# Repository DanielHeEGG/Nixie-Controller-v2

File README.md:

# Nixie Clock Controller v2
The most overpowered 6-tube nixie clock controller ever created.

For more details on the project, see [Hackaday Page](https://hackaday.io/project/181819-nixie-clock-controller-v2).

Sockets designed to work with this controller are in the [NCv2-Sockets](https://github.com/DanielHeEGG/NCv2-Sockets) repo.

Firmware files are in the [NCv2-Firmware](https://github.com/DanielHeEGG/NCv2-Firmware) repo.

> **WARNING:**
> This project contains EXPOSED and UNMARKED HIGH VOLTAGE contacts, replicate at your own risk.
## License
This project is licensed under the [Creative Commons Attribution-ShareAlike 4.0 International License](http://creativecommons.org/licenses/by-sa/4.0/).

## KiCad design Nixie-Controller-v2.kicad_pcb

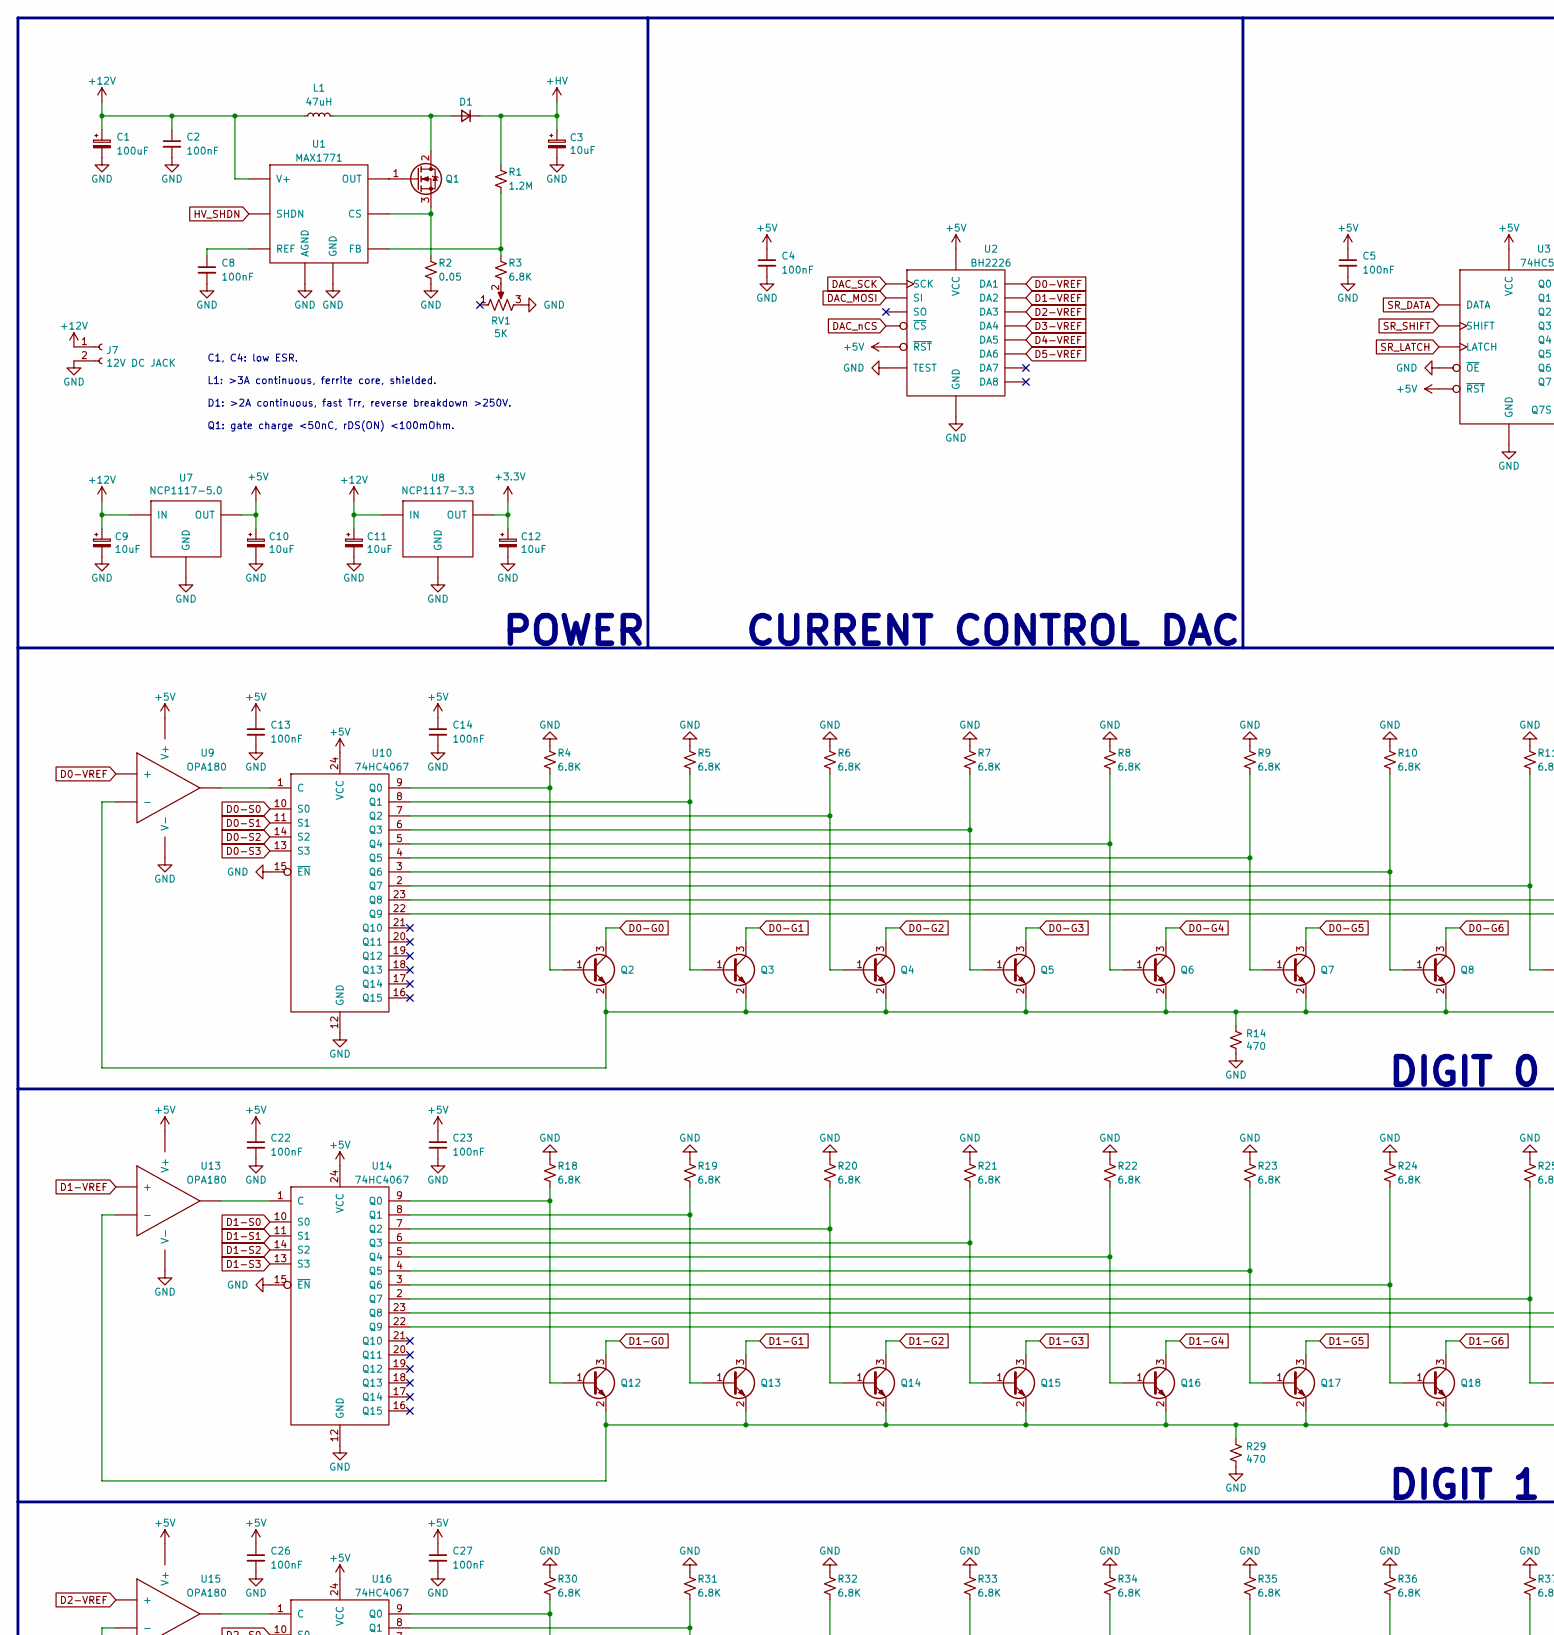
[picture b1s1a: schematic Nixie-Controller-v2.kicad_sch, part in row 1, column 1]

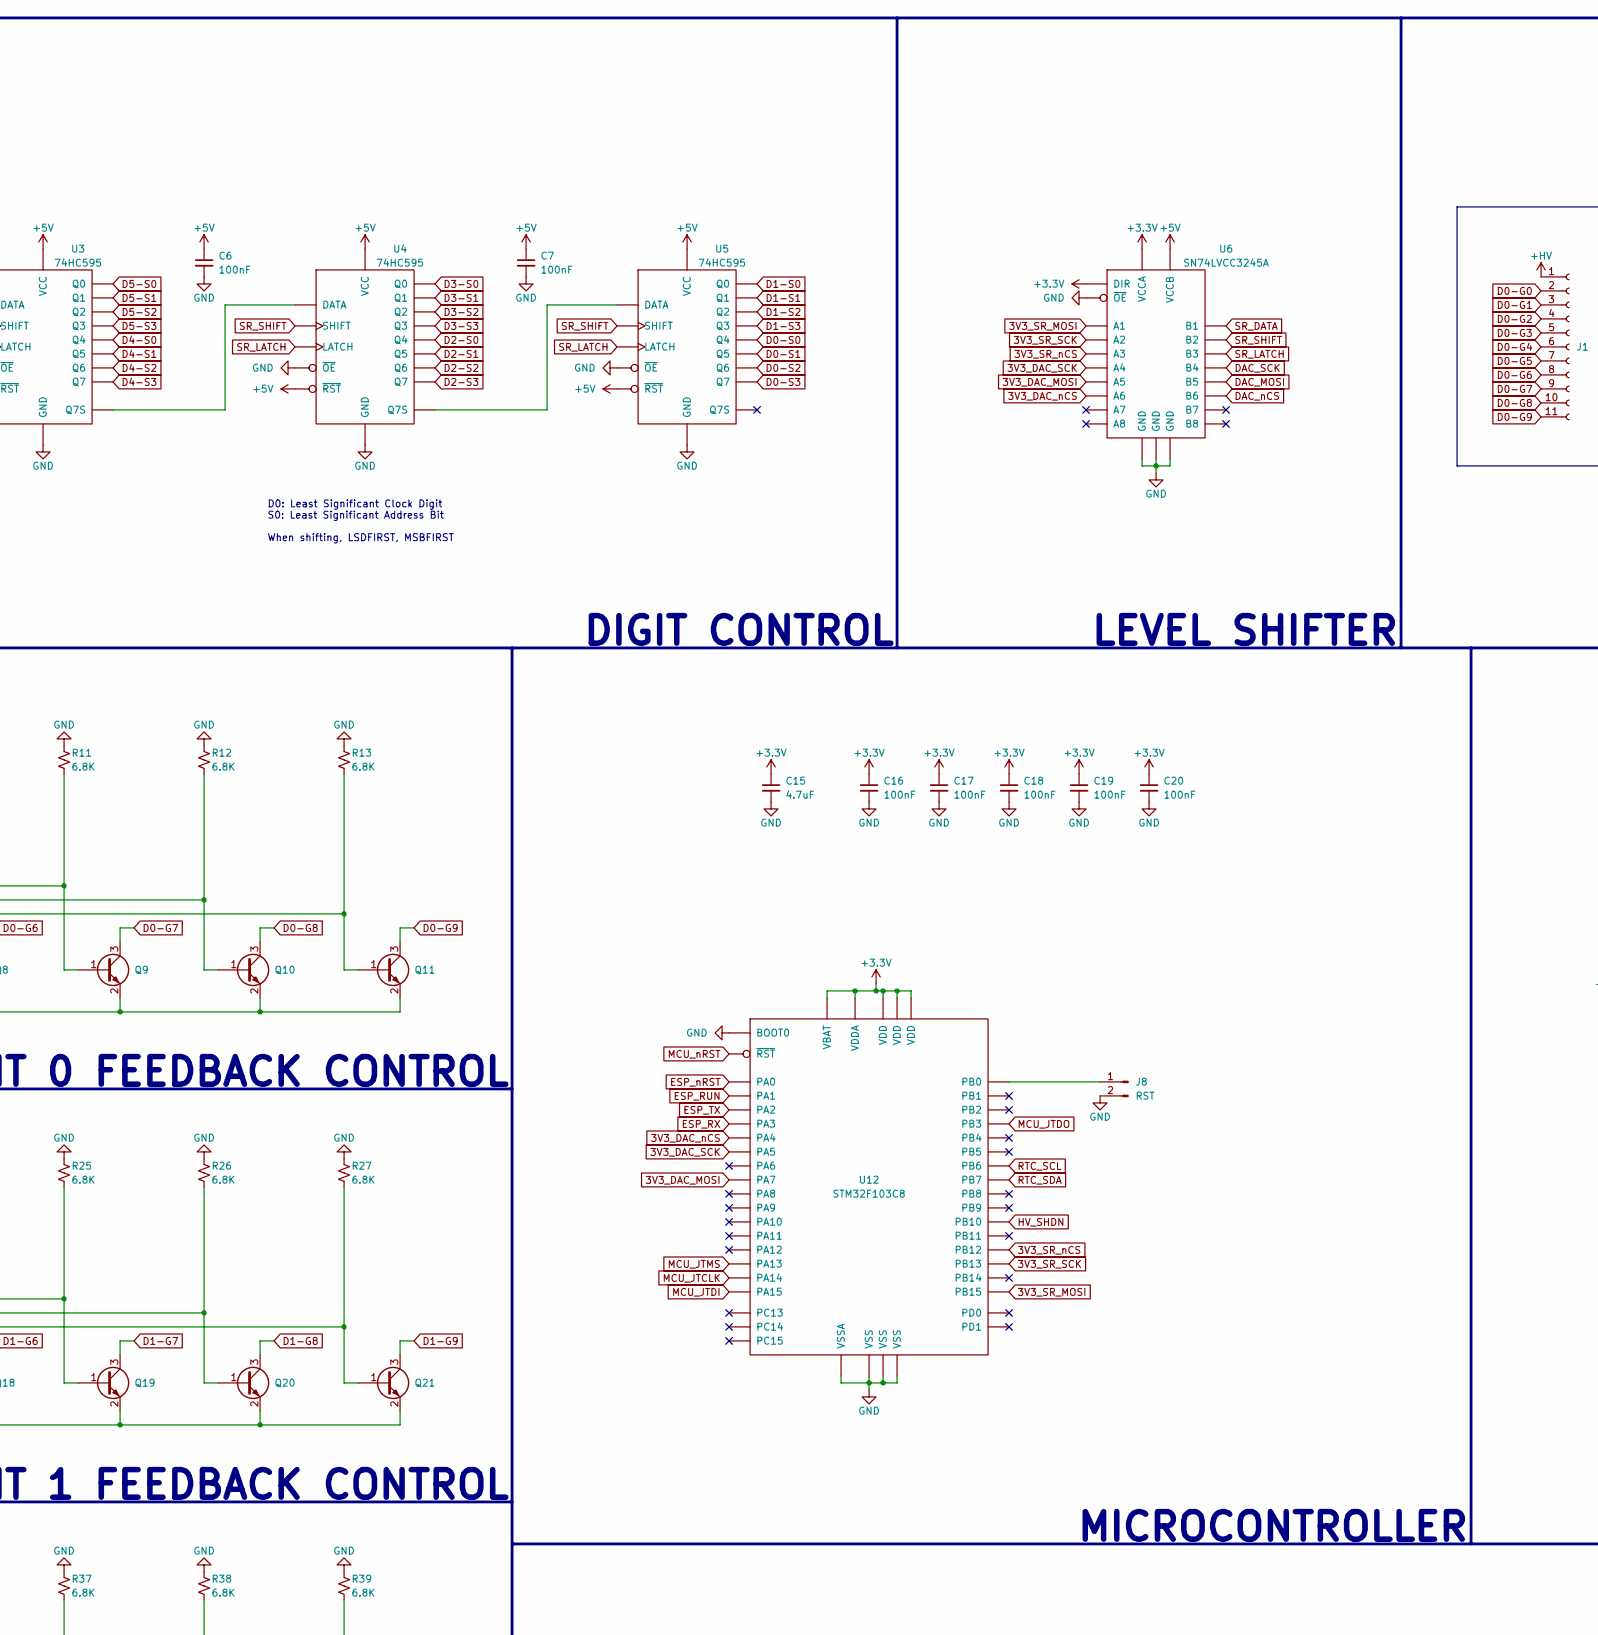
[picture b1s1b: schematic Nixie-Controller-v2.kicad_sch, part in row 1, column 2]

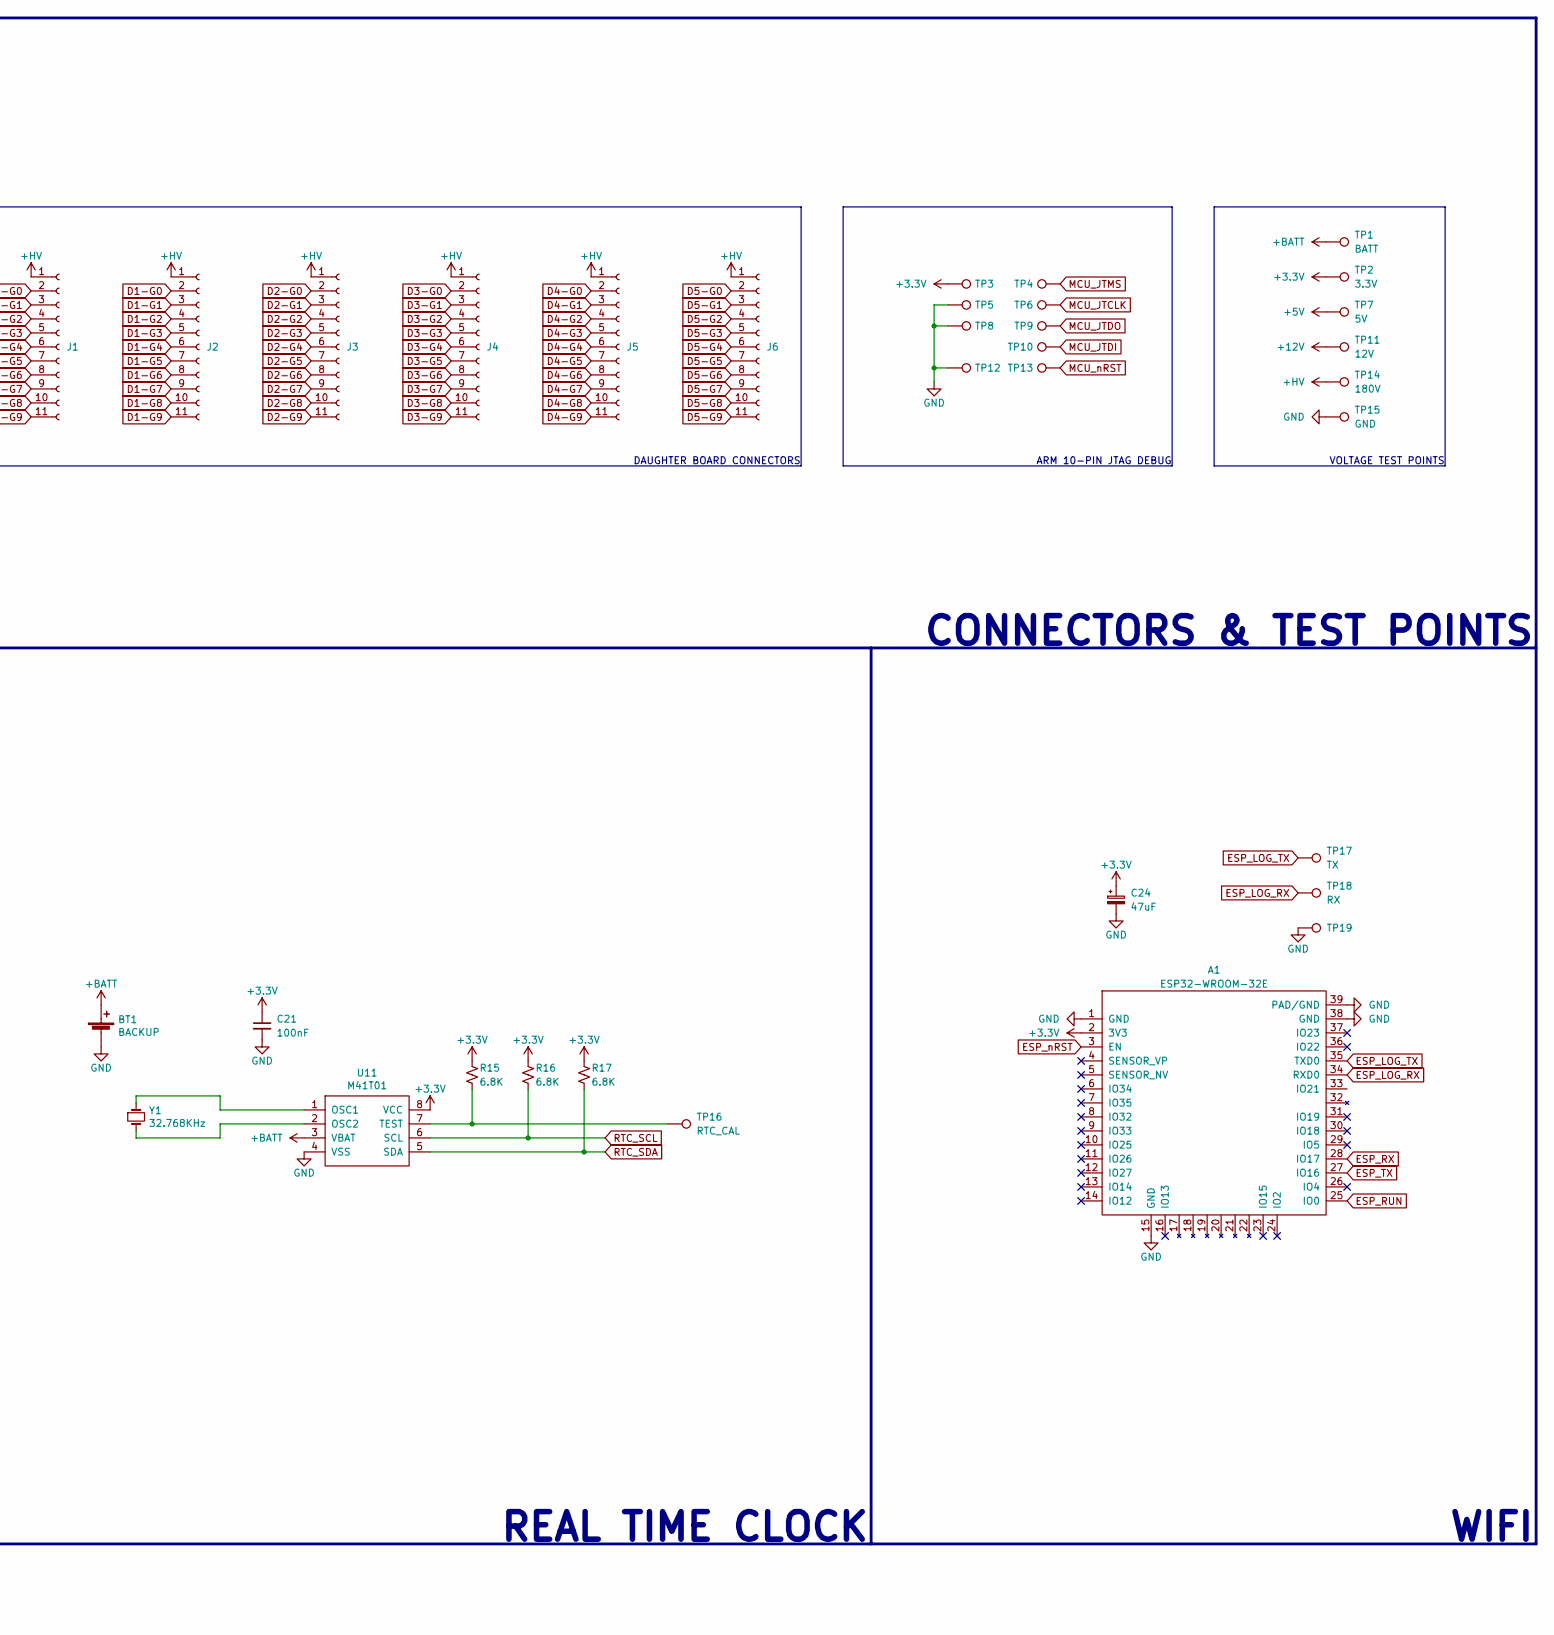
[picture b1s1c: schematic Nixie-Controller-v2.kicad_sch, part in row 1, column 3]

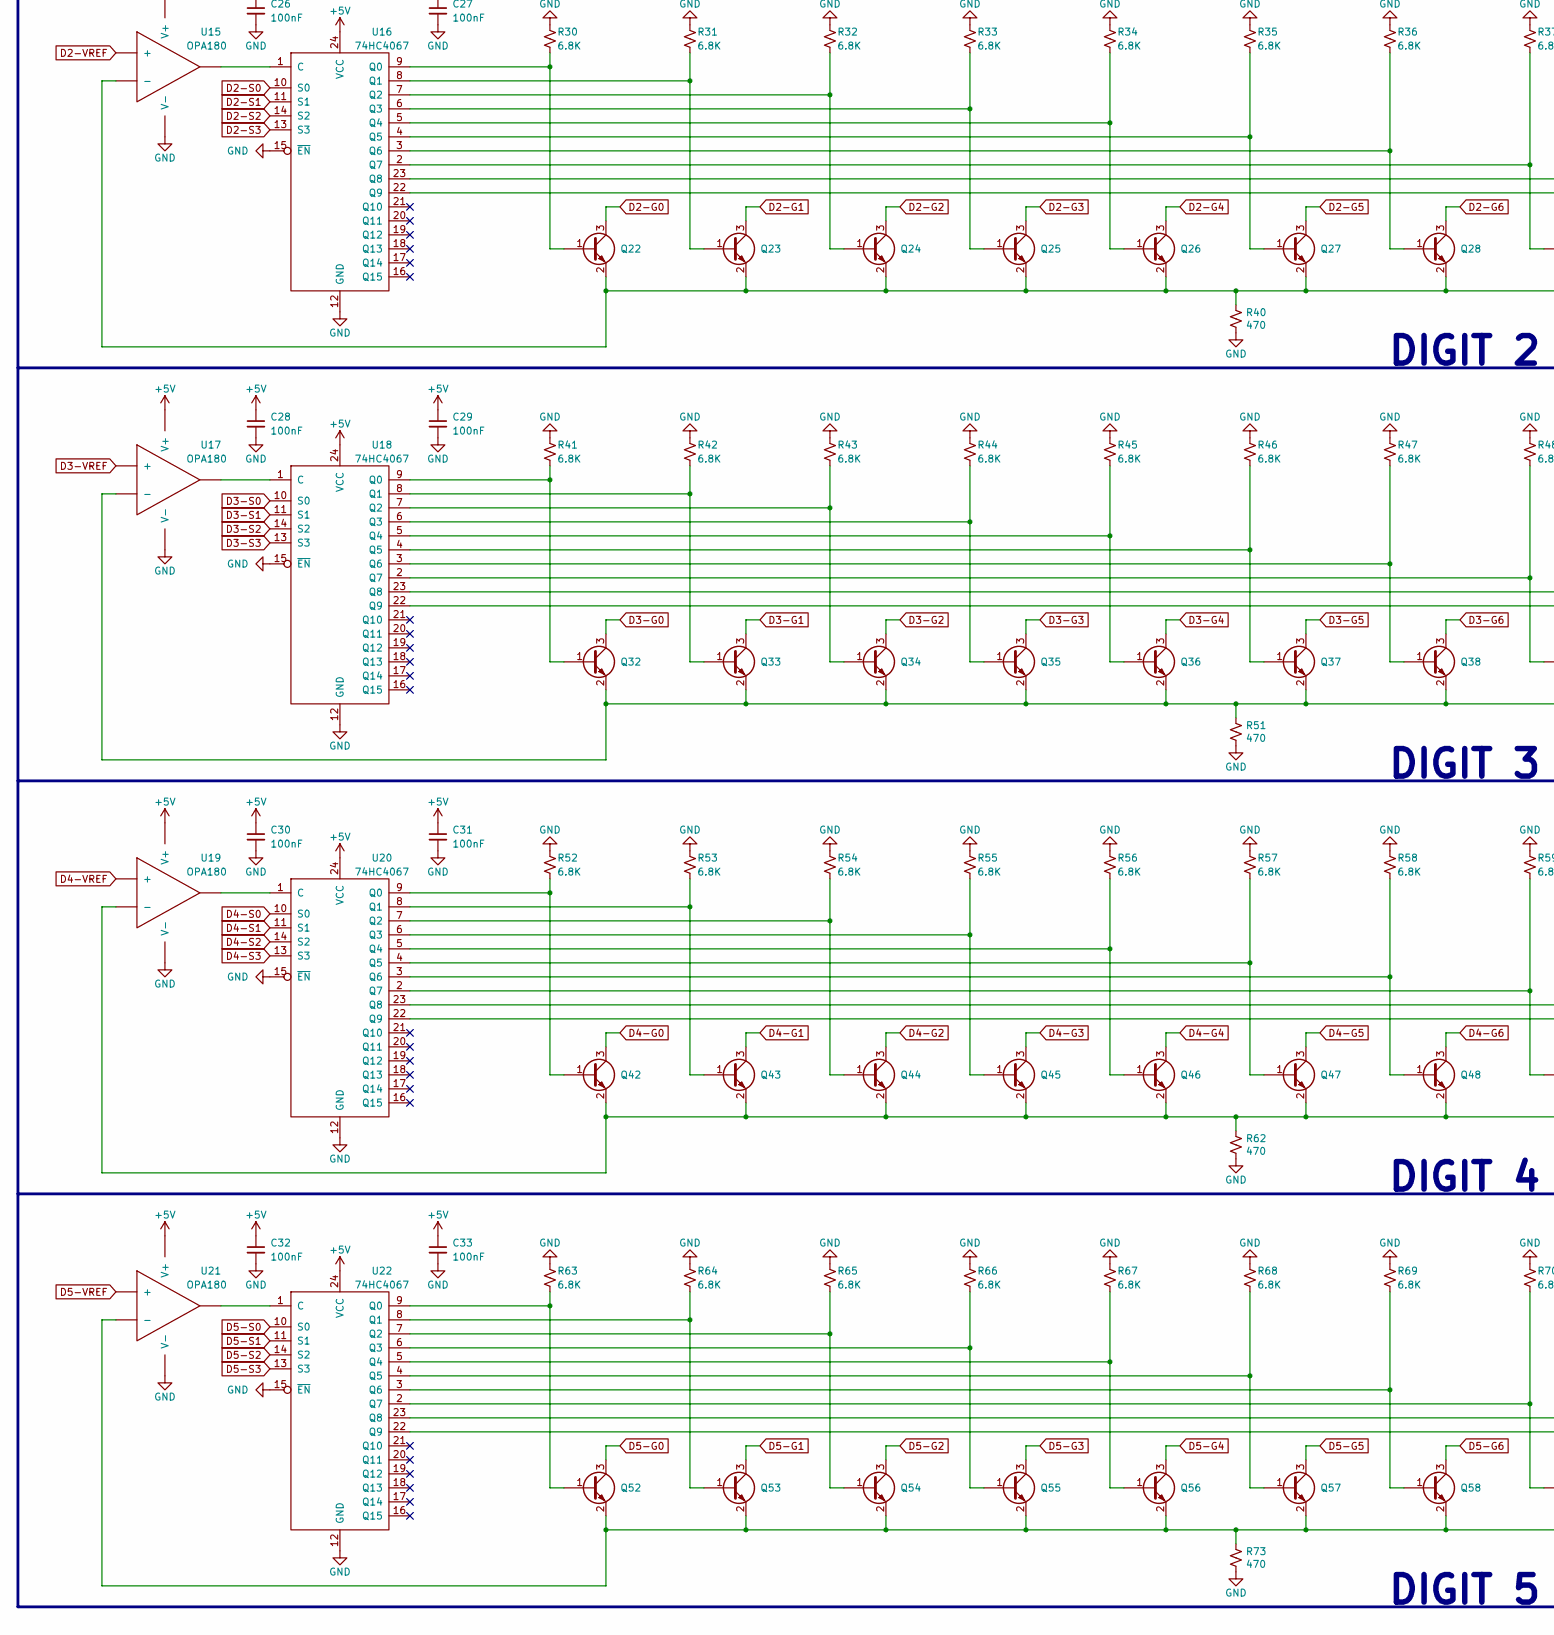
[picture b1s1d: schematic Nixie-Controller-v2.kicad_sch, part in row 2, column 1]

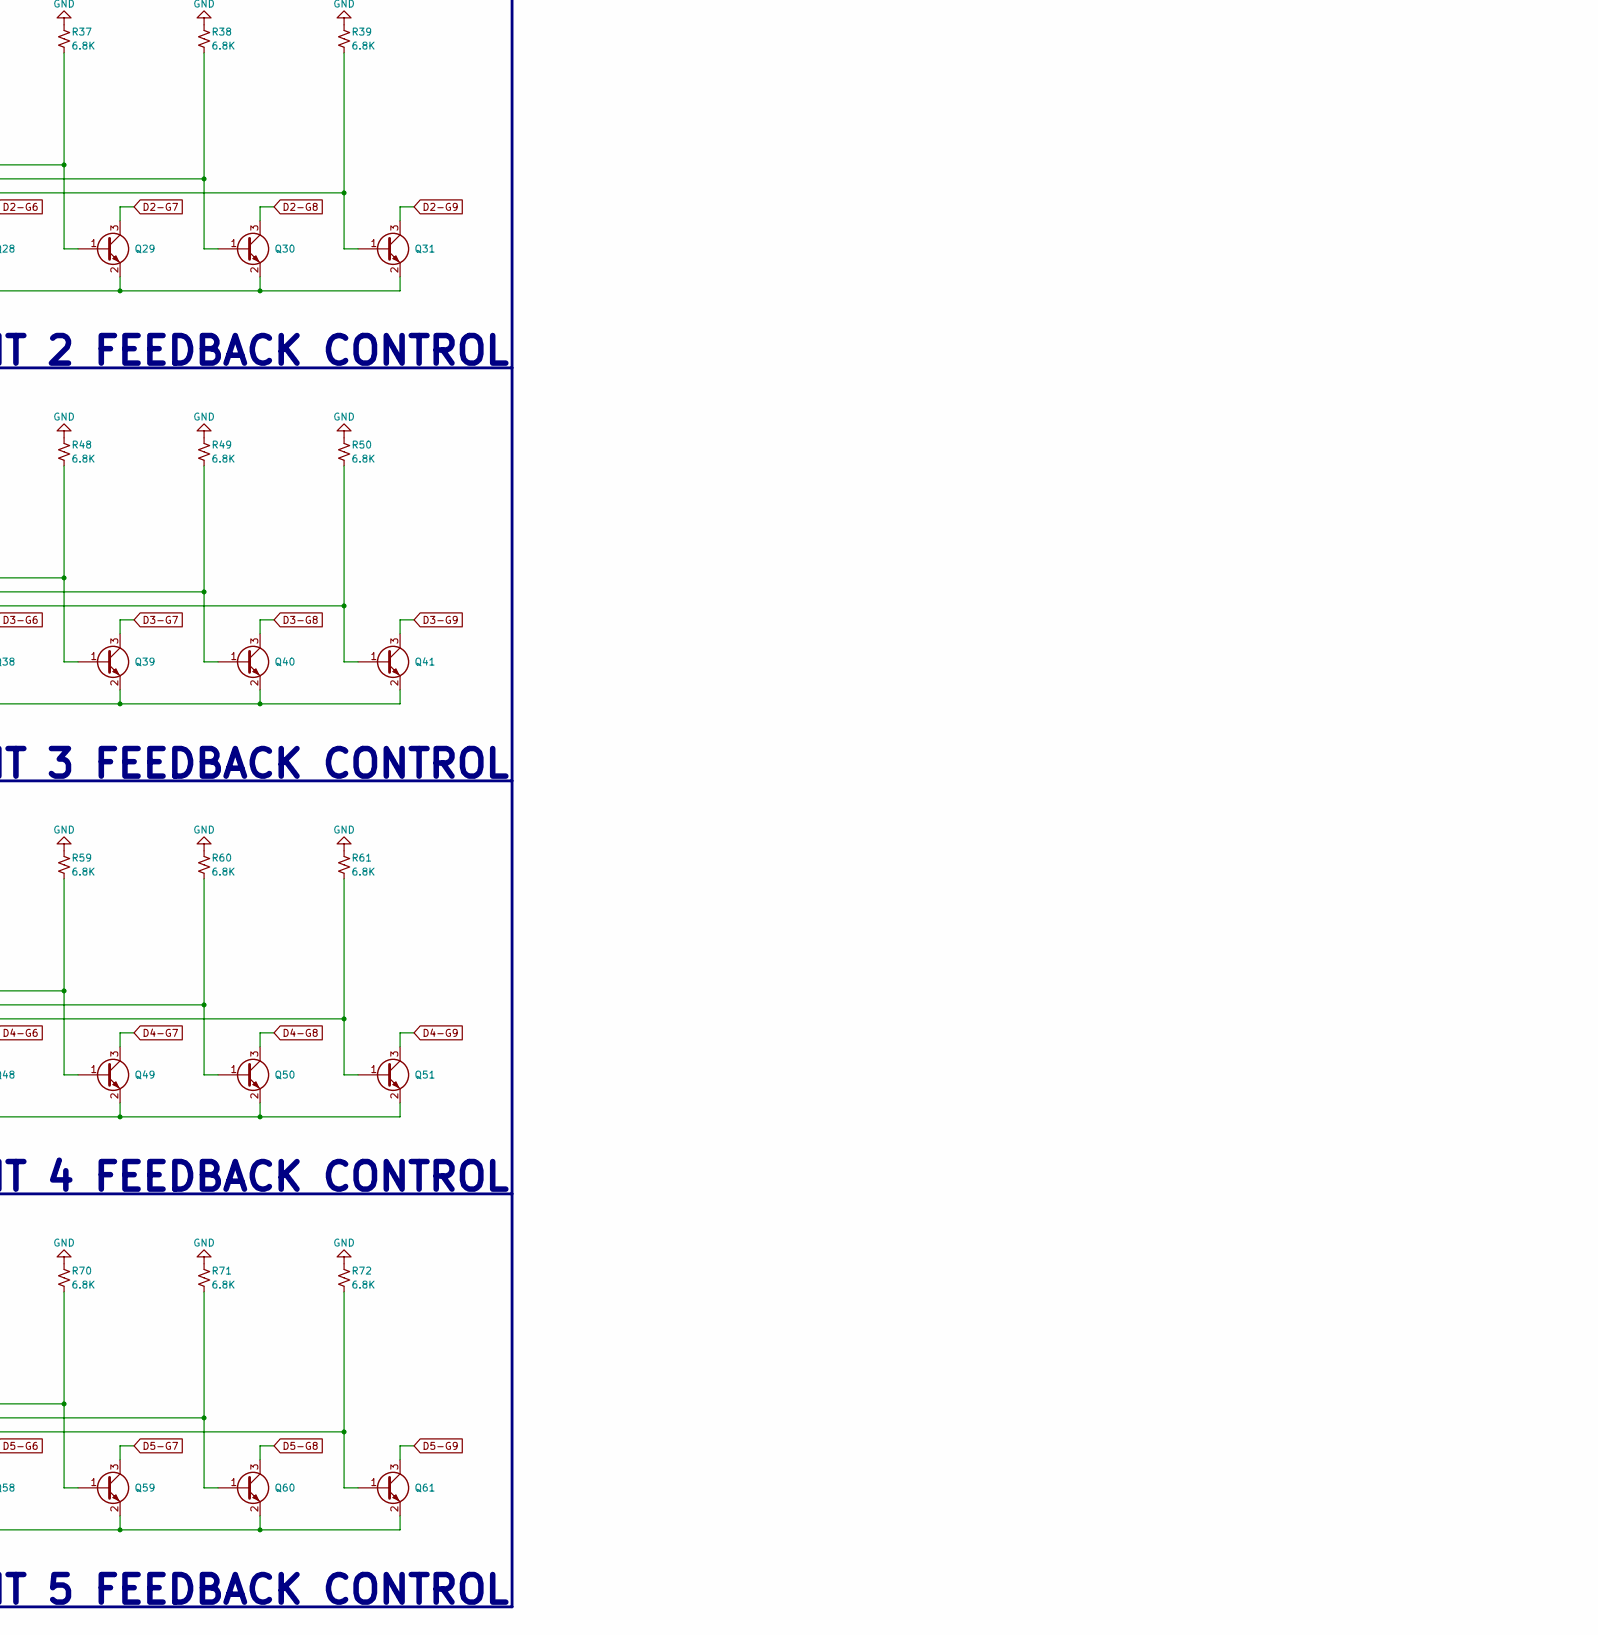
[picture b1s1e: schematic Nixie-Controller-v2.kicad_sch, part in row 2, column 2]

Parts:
A1: ESP32-WROOM-32E; ESP32-WROOM-32
BT1: BACKUP; BatteryHolder_Keystone_1058_1x2032; Part# 1058
C1: 100uF; CP_EIA-7343-43_Kemet-X; Part# T510X107M020ATE045
C2, C4, C5, C6, C7, C8, C13, C14, C16, C17, C18, C19, C20, C21, C22, C23, C26, C27, C28, C29, C30, C31, C32, C33: 100nF; C_0402_1005Metric; Part# CC0402KRX7R8BB104
C3: 10uF; CP_Elec_10x10; Part# UUX2E100MNL1GS
C9, C10, C11, C12: 10uF; CP_Elec_6.3x7.7; Part# UUL1H100MCL1GS
C15: 4.7uF; C_0603_1608Metric; Part# CC0603MRX5R5BB475
C24: 47uF; CP_Elec_5x5.3; Part# UWF0J470MCL1GB
D1: D_SMB; Part# ES2F
J1, J2, J3, J4, J5, J6: PinSocket_1x11_P2.54mm_Vertical
J7: 12V DC JACK; BarrelJack_Horizontal
J8: RST; PinHeader_1x02_P2.54mm_Vertical
L1: 47uH; L_Bourns_SRR1210A; Part# SRR1210A-470M
Q1: TO-252-2; Part# IXFY26N30X3
Q2, Q3, Q4, Q5, Q6, Q7, Q8, Q9, Q10, Q11, Q12, Q13, Q14, Q15, Q16, Q17, Q18, Q19, Q20, Q21, Q22, Q23, Q24, Q25, Q26, Q27, Q28, Q29, Q30, Q31, Q32, Q33, Q34, Q35, Q36, Q37, Q38, Q39, Q40, Q41, Q42, Q43, Q44, Q45, Q46, Q47, Q48, Q49, Q50, Q51, Q52, Q53, Q54, Q55, Q56, Q57, Q58, Q59, Q60, Q61: SOT-23; Part# MMBTA42
R1: 1.2M; R_0805_2012Metric; Part# RC0805FR-071M2L
R2: 0.05; R_2010_5025Metric; Part# PE2010FKE070R05L
R3, R4, R5, R6, R7, R8, R9, R10, R11, R12, R13, R15, R16, R17, R18, R19, R20, R21, R22, R23, R24, R25, R26, R27, R30, R31, R32, R33, R34, R35, R36, R37, R38, R39, R41, R42, R43, R44, R45, R46, R47, R48, R49, R50, R52, R53, R54, R55, R56, R57, R58, R59, R60, R61, R63, R64, R65, R66, R67, R68, R69, R70, R71, R72: 6.8K; R_0402_1005Metric; Part# RC0402FR-076K8L
R14, R29, R40, R51, R62, R73: 470; R_0402_1005Metric; Part# RC0402FR-07470RL
RV1: 5K; Potentiometer_Bourns_3214J_Horizontal; Part# 3214J-1-502E
TP1: BATT; TestPoint_Pad_D1.5mm
TP2: 3.3V; TestPoint_Pad_D1.5mm
TP3, TP4, TP5, TP6, TP8, TP9, TP10, TP12, TP13, TP19: TestPoint_Pad_D1.5mm
TP7: 5V; TestPoint_Pad_D1.5mm
TP11: 12V; TestPoint_Pad_D1.5mm
TP14: 180V; TestPoint_Pad_D1.5mm
TP15: GND; TestPoint_Pad_D1.5mm
TP16: RTC_CAL; TestPoint_Pad_D1.5mm
TP17: TX; TestPoint_Pad_D1.5mm
TP18: RX; TestPoint_Pad_D1.5mm
U1: MAX1771; SOIC-8_3.9x4.9mm_P1.27mm; Part# MAX1771CSA
U2: BH2226; SOIC-16_4.55x10.3mm_P1.27mm; Part# BH2226F-E2
U3, U4, U5: 74HC595; SOIC-16_3.9x9.9mm_P1.27mm; Part# CD74HC595M
U6: SN74LVCC3245A; SO-24_5.3x15mm_P1.27mm; Part# SN74LVCC3245ANSR
U7: NCP1117-5.0; SOT-223-3_TabPin2; Part# NCP1117LPST50T3G
U8: NCP1117-3.3; SOT-223-3_TabPin2; Part# NCP1117LPST33T3G
U9, U13, U15, U17, U19, U21: OPA180; SOT-23-5; Part# OPA180IDBVT
U10, U14, U16, U18, U20, U22: 74HC4067; SOIC-24W_7.5x15.4mm_P1.27mm; Part# CD74HC4067M
U11: M41T01; SOIC-8_3.9x4.9mm_P1.27mm; Part# M41T01M6F
U12: STM32F103C8; LQFP-48_7x7mm_P0.5mm; Part# STM32F103C8T6
Y1: 32.768KHz; Crystal_SMD_2012-2Pin_2.0x1.2mm; Part# SC20S-12.5PF20PPM

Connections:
3V3_DAC_MOSI: U6.7 (A5), U12.17 (PA7)
3V3_DAC_SCK: U6.6 (A4), U12.15 (PA5)
3V3_DAC_nCS: U6.8 (A6), U12.14 (PA4)
3V3_SR_MOSI: U6.3 (A1), U12.28 (PB15)
3V3_SR_SCK: U6.4 (A2), U12.26 (PB13)
3V3_SR_nCS: U6.5 (A3), U12.25 (PB12)
+3V3: A1.2 (3V3), C12.1, C15.1, C16.1, C17.1, C18.1, C19.1, C20.1, C21.1, C24.1, R15.1, R16.1, R17.1, TP2.1, TP3.1, U6.1 (VCCA), U6.2 (DIR), U8.2 (OUT), U11.8 (VCC), U12.1 (VBAT), U12.9 (VDDA), U12.24 (VDD), U12.36 (VDD), U12.48 (VDD)
+5V: C4.1, C5.1, C6.1, C7.1, C10.1, C13.1, C14.1, C22.1, C23.1, C26.1, C27.1, C28.1, C29.1, C30.1, C31.1, C32.1, C33.1, TP7.1, U2.9 (VCC), U2.10 (~RST), U3.10 (~RST), U3.16 (VCC), U4.10 (~RST), U4.16 (VCC), U5.10 (~RST), U5.16 (VCC), U6.24 (VCCB), U7.2 (OUT), U9.5 (V+), U10.24 (VCC), U13.5 (V+), U14.24 (VCC), U15.5 (V+), U16.24 (VCC), U17.5 (V+), U18.24 (VCC), U19.5 (V+), U20.24 (VCC), U21.5 (V+), U22.24 (VCC)
+12V: C1.1, C2.1, C9.1, C11.1, J7.1, L1.1, TP11.1, U1.2 (V+), U7.3 (IN), U8.3 (IN)
+BATT: BT1.1 (+), TP1.1, U11.3 (VBAT)
+HV: C3.1, D1.1 (K), J1.1, J2.1, J3.1, J4.1, J5.1, J6.1, R1.1, TP14.1
D0-G0: J1.2, Q2.3 (C)
D0-G1: J1.3, Q3.3 (C)
D0-G2: J1.4, Q4.3 (C)
D0-G3: J1.5, Q5.3 (C)
D0-G4: J1.6, Q6.3 (C)
D0-G5: J1.7, Q7.3 (C)
D0-G6: J1.8, Q8.3 (C)
D0-G7: J1.9, Q9.3 (C)
D0-G8: J1.10, Q10.3 (C)
D0-G9: J1.11, Q11.3 (C)
D0-S0: U5.4 (Q4), U10.10 (S0)
D0-S1: U5.5 (Q5), U10.11 (S1)
D0-S2: U5.6 (Q6), U10.14 (S2)
D0-S3: U5.7 (Q7), U10.13 (S3)
D0-VREF: U2.1 (DA1), U9.3 (+)
D1-G0: J2.2, Q12.3 (C)
D1-G1: J2.3, Q13.3 (C)
D1-G2: J2.4, Q14.3 (C)
D1-G3: J2.5, Q15.3 (C)
D1-G4: J2.6, Q16.3 (C)
D1-G5: J2.7, Q17.3 (C)
D1-G6: J2.8, Q18.3 (C)
D1-G7: J2.9, Q19.3 (C)
D1-G8: J2.10, Q20.3 (C)
D1-G9: J2.11, Q21.3 (C)
D1-S0: U5.15 (Q0), U14.10 (S0)
D1-S1: U5.1 (Q1), U14.11 (S1)
D1-S2: U5.2 (Q2), U14.14 (S2)
D1-S3: U5.3 (Q3), U14.13 (S3)
D1-VREF: U2.2 (DA2), U13.3 (+)
D2-G0: J3.2, Q22.3 (C)
D2-G1: J3.3, Q23.3 (C)
D2-G2: J3.4, Q24.3 (C)
D2-G3: J3.5, Q25.3 (C)
D2-G4: J3.6, Q26.3 (C)
D2-G5: J3.7, Q27.3 (C)
D2-G6: J3.8, Q28.3 (C)
D2-G7: J3.9, Q29.3 (C)
D2-G8: J3.10, Q30.3 (C)
D2-G9: J3.11, Q31.3 (C)
D2-S0: U4.4 (Q4), U16.10 (S0)
D2-S1: U4.5 (Q5), U16.11 (S1)
D2-S2: U4.6 (Q6), U16.14 (S2)
D2-S3: U4.7 (Q7), U16.13 (S3)
D2-VREF: U2.3 (DA3), U15.3 (+)
D3-G0: J4.2, Q32.3 (C)
D3-G1: J4.3, Q33.3 (C)
D3-G2: J4.4, Q34.3 (C)
D3-G3: J4.5, Q35.3 (C)
D3-G4: J4.6, Q36.3 (C)
D3-G5: J4.7, Q37.3 (C)
D3-G6: J4.8, Q38.3 (C)
D3-G7: J4.9, Q39.3 (C)
D3-G8: J4.10, Q40.3 (C)
D3-G9: J4.11, Q41.3 (C)
D3-S0: U4.15 (Q0), U18.10 (S0)
D3-S1: U4.1 (Q1), U18.11 (S1)
D3-S2: U4.2 (Q2), U18.14 (S2)
D3-S3: U4.3 (Q3), U18.13 (S3)
D3-VREF: U2.4 (DA4), U17.3 (+)
D4-G0: J5.2, Q42.3 (C)
D4-G1: J5.3, Q43.3 (C)
D4-G2: J5.4, Q44.3 (C)
D4-G3: J5.5, Q45.3 (C)
D4-G4: J5.6, Q46.3 (C)
D4-G5: J5.7, Q47.3 (C)
D4-G6: J5.8, Q48.3 (C)
D4-G7: J5.9, Q49.3 (C)
D4-G8: J5.10, Q50.3 (C)
D4-G9: J5.11, Q51.3 (C)
D4-S0: U3.4 (Q4), U20.10 (S0)
D4-S1: U3.5 (Q5), U20.11 (S1)
D4-S2: U3.6 (Q6), U20.14 (S2)
D4-S3: U3.7 (Q7), U20.13 (S3)
D4-VREF: U2.5 (DA5), U19.3 (+)
D5-G0: J6.2, Q52.3 (C)
D5-G1: J6.3, Q53.3 (C)
D5-G2: J6.4, Q54.3 (C)
D5-G3: J6.5, Q55.3 (C)
D5-G4: J6.6, Q56.3 (C)
D5-G5: J6.7, Q57.3 (C)
D5-G6: J6.8, Q58.3 (C)
D5-G7: J6.9, Q59.3 (C)
D5-G8: J6.10, Q60.3 (C)
D5-G9: J6.11, Q61.3 (C)
D5-S0: U3.15 (Q0), U22.10 (S0)
D5-S1: U3.1 (Q1), U22.11 (S1)
D5-S2: U3.2 (Q2), U22.14 (S2)
D5-S3: U3.3 (Q3), U22.13 (S3)
D5-VREF: U2.6 (DA6), U21.3 (+)
DAC_MOSI: U2.14 (SI), U6.17 (B5)
DAC_SCK: U2.13 (SCK), U6.18 (B4)
DAC_nCS: U2.12 (~CS), U6.16 (B6)
ESP_LOG_RX: A1.34 (RXD0), TP18.1
ESP_LOG_TX: A1.35 (TXD0), TP17.1
ESP_RUN: A1.25 (IO0), U12.11 (PA1)
ESP_RX: A1.28 (IO17), U12.13 (PA3)
ESP_TX: A1.27 (IO16), U12.12 (PA2)
ESP_nRST: A1.3 (EN), U12.10 (PA0)
GND: A1.1 (GND), A1.15 (GND), A1.38 (GND), A1.39 (PAD/GND), BT1.2 (-), C1.2, C2.2, C3.2, C4.2, C5.2, C6.2, C7.2, C8.2, C9.2, C10.2, C11.2, C12.2, C13.2, C14.2, C15.2, C16.2, C17.2, C18.2, C19.2, C20.2, C21.2, C22.2, C23.2, C24.2, C26.2, C27.2, C28.2, C29.2, C30.2, C31.2, C32.2, C33.2, J7.2, J8.2, R2.2, R4.1, R5.1, R6.1, R7.1, R8.1, R9.1, R10.1, R11.1, R12.1, R13.1, R14.2, R18.1, R19.1, R20.1, R21.1, R22.1, R23.1, R24.1, R25.1, R26.1, R27.1, R29.2, R30.1, R31.1, R32.1, R33.1, R34.1, R35.1, R36.1, R37.1, R38.1, R39.1, R40.2, R41.1, R42.1, R43.1, R44.1, R45.1, R46.1, R47.1, R48.1, R49.1, R50.1, R51.2, R52.1, R53.1, R54.1, R55.1, R56.1, R57.1, R58.1, R59.1, R60.1, R61.1, R62.2, R63.1, R64.1, R65.1, R66.1, R67.1, R68.1, R69.1, R70.1, R71.1, R72.1, R73.2, RV1.3, TP5.1, TP8.1, TP12.1, TP15.1, TP19.1, U1.6 (AGND), U1.7 (GND), U2.11 (TEST), U2.16 (GND), U3.8 (GND), U3.13 (~OE), U4.8 (GND), U4.13 (~OE), U5.8 (GND), U5.13 (~OE), U6.11 (GND), U6.12 (GND), U6.13 (GND), U6.22 (~OE), U7.1 (GND), U8.1 (GND), U9.2 (V-), U10.12 (GND), U10.15 (~EN), U11.4 (VSS), U12.8 (VSSA), U12.23 (VSS), U12.35 (VSS), U12.44 (BOOT0), U12.47 (VSS), U13.2 (V-), U14.12 (GND), U14.15 (~EN), U15.2 (V-), U16.12 (GND), U16.15 (~EN), U17.2 (V-), U18.12 (GND), U18.15 (~EN), U19.2 (V-), U20.12 (GND), U20.15 (~EN), U21.2 (V-), U22.12 (GND), U22.15 (~EN)
HV_SHDN: U1.4 (SHDN), U12.21 (PB10)
MCU_JTCLK: TP6.1, U12.37 (PA14)
MCU_JTDI: TP10.1, U12.38 (PA15)
MCU_JTDO: TP9.1, U12.39 (PB3)
MCU_JTMS: TP4.1, U12.34 (PA13)
MCU_nRST: TP13.1, U12.7 (~RST)
unnamed: C8.1, U1.5 (REF)
unnamed: D1.2 (A), L1.2, Q1.2 (D)
unnamed: J8.1, U12.18 (PB0)
unnamed: Q1.1 (G), U1.1 (OUT)
unnamed: Q1.3 (S), R2.1, U1.8 (CS)
unnamed: Q2.1 (B), R4.2, U10.9 (Q0)
unnamed: Q3.1 (B), R5.2, U10.8 (Q1)
unnamed: Q4.1 (B), R6.2, U10.7 (Q2)
unnamed: Q5.1 (B), R7.2, U10.6 (Q3)
unnamed: Q6.1 (B), R8.2, U10.5 (Q4)
unnamed: Q7.1 (B), R9.2, U10.4 (Q5)
unnamed: Q8.1 (B), R10.2, U10.3 (Q6)
unnamed: Q9.1 (B), R11.2, U10.2 (Q7)
unnamed: Q10.1 (B), R12.2, U10.23 (Q8)
unnamed: Q2.2 (E), Q3.2 (E), Q4.2 (E), Q5.2 (E), Q6.2 (E), Q7.2 (E), Q8.2 (E), Q9.2 (E), Q10.2 (E), Q11.2 (E), R14.1, U9.4 (-)
unnamed: Q11.1 (B), R13.2, U10.22 (Q9)
unnamed: Q12.1 (B), R18.2, U14.9 (Q0)
unnamed: Q12.2 (E), Q13.2 (E), Q14.2 (E), Q15.2 (E), Q16.2 (E), Q17.2 (E), Q18.2 (E), Q19.2 (E), Q20.2 (E), Q21.2 (E), R29.1, U13.4 (-)
unnamed: Q13.1 (B), R19.2, U14.8 (Q1)
unnamed: Q14.1 (B), R20.2, U14.7 (Q2)
unnamed: Q15.1 (B), R21.2, U14.6 (Q3)
unnamed: Q16.1 (B), R22.2, U14.5 (Q4)
unnamed: Q17.1 (B), R23.2, U14.4 (Q5)
unnamed: Q18.1 (B), R24.2, U14.3 (Q6)
unnamed: Q19.1 (B), R25.2, U14.2 (Q7)
unnamed: Q20.1 (B), R26.2, U14.23 (Q8)
unnamed: Q21.1 (B), R27.2, U14.22 (Q9)
unnamed: Q22.1 (B), R30.2, U16.9 (Q0)
unnamed: Q22.2 (E), Q23.2 (E), Q24.2 (E), Q25.2 (E), Q26.2 (E), Q27.2 (E), Q28.2 (E), Q29.2 (E), Q30.2 (E), Q31.2 (E), R40.1, U15.4 (-)
unnamed: Q23.1 (B), R31.2, U16.8 (Q1)
unnamed: Q24.1 (B), R32.2, U16.7 (Q2)
unnamed: Q25.1 (B), R33.2, U16.6 (Q3)
unnamed: Q26.1 (B), R34.2, U16.5 (Q4)
unnamed: Q27.1 (B), R35.2, U16.4 (Q5)
unnamed: Q28.1 (B), R36.2, U16.3 (Q6)
unnamed: Q29.1 (B), R37.2, U16.2 (Q7)
unnamed: Q30.1 (B), R38.2, U16.23 (Q8)
unnamed: Q31.1 (B), R39.2, U16.22 (Q9)
unnamed: Q32.1 (B), R41.2, U18.9 (Q0)
unnamed: Q32.2 (E), Q33.2 (E), Q34.2 (E), Q35.2 (E), Q36.2 (E), Q37.2 (E), Q38.2 (E), Q39.2 (E), Q40.2 (E), Q41.2 (E), R51.1, U17.4 (-)
unnamed: Q33.1 (B), R42.2, U18.8 (Q1)
unnamed: Q34.1 (B), R43.2, U18.7 (Q2)
unnamed: Q35.1 (B), R44.2, U18.6 (Q3)
unnamed: Q36.1 (B), R45.2, U18.5 (Q4)
unnamed: Q37.1 (B), R46.2, U18.4 (Q5)
unnamed: Q38.1 (B), R47.2, U18.3 (Q6)
unnamed: Q39.1 (B), R48.2, U18.2 (Q7)
unnamed: Q40.1 (B), R49.2, U18.23 (Q8)
unnamed: Q41.1 (B), R50.2, U18.22 (Q9)
unnamed: Q42.1 (B), R52.2, U20.9 (Q0)
unnamed: Q42.2 (E), Q43.2 (E), Q44.2 (E), Q45.2 (E), Q46.2 (E), Q47.2 (E), Q48.2 (E), Q49.2 (E), Q50.2 (E), Q51.2 (E), R62.1, U19.4 (-)
unnamed: Q43.1 (B), R53.2, U20.8 (Q1)
unnamed: Q44.1 (B), R54.2, U20.7 (Q2)
unnamed: Q45.1 (B), R55.2, U20.6 (Q3)
unnamed: Q46.1 (B), R56.2, U20.5 (Q4)
unnamed: Q47.1 (B), R57.2, U20.4 (Q5)
unnamed: Q48.1 (B), R58.2, U20.3 (Q6)
unnamed: Q49.1 (B), R59.2, U20.2 (Q7)
unnamed: Q50.1 (B), R60.2, U20.23 (Q8)
unnamed: Q51.1 (B), R61.2, U20.22 (Q9)
unnamed: Q52.1 (B), R63.2, U22.9 (Q0)
unnamed: Q52.2 (E), Q53.2 (E), Q54.2 (E), Q55.2 (E), Q56.2 (E), Q57.2 (E), Q58.2 (E), Q59.2 (E), Q60.2 (E), Q61.2 (E), R73.1, U21.4 (-)
unnamed: Q53.1 (B), R64.2, U22.8 (Q1)
unnamed: Q54.1 (B), R65.2, U22.7 (Q2)
unnamed: Q55.1 (B), R66.2, U22.6 (Q3)
unnamed: Q56.1 (B), R67.2, U22.5 (Q4)
unnamed: Q57.1 (B), R68.2, U22.4 (Q5)
unnamed: Q58.1 (B), R69.2, U22.3 (Q6)
unnamed: Q59.1 (B), R70.2, U22.2 (Q7)
unnamed: Q60.1 (B), R71.2, U22.23 (Q8)
unnamed: Q61.1 (B), R72.2, U22.22 (Q9)
unnamed: R1.2, R3.1, U1.3 (FB)
unnamed: R3.2, RV1.2
unnamed: R15.2, TP16.1, U11.7 (TEST)
unnamed: U3.9 (Q7S), U4.14 (DATA)
unnamed: U4.9 (Q7S), U5.14 (DATA)
unnamed: U9.1, U10.1 (C)
unnamed: U11.1 (OSC1), Y1.1
unnamed: U11.2 (OSC2), Y1.2
unnamed: U13.1, U14.1 (C)
unnamed: U15.1, U16.1 (C)
unnamed: U17.1, U18.1 (C)
unnamed: U19.1, U20.1 (C)
unnamed: U21.1, U22.1 (C)
RTC_SCL: R16.2, U11.6 (SCL), U12.42 (PB6)
RTC_SDA: R17.2, U11.5 (SDA), U12.43 (PB7)
SR_DATA: U3.14 (DATA), U6.21 (B1)
SR_LATCH: U3.12 (LATCH), U4.12 (LATCH), U5.12 (LATCH), U6.19 (B3)
SR_SHIFT: U3.11 (SHIFT), U4.11 (SHIFT), U5.11 (SHIFT), U6.20 (B2)

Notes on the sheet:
CONNECTORS & TEST POINTS
DIGIT 0 FEEDBACK CONTROL
DAUGHTER BOARD CONNECTORS
VOLTAGE TEST POINTS
D0: Least Significant Clock Digit S0: Least Significant Address Bit When shifting, LSDFIRST, MSBFIRST
DIGIT 4 FEEDBACK CONTROL
CURRENT CONTROL DAC
WIFI
DIGIT 5 FEEDBACK CONTROL
DIGIT 2 FEEDBACK CONTROL
MICROCONTROLLER
REAL TIME CLOCK
DIGIT 3 FEEDBACK CONTROL
ARM 10-PIN JTAG DEBUG
LEVEL SHIFTER
POWER
C1, C4: low ESR. L1: >3A continuous, ferrite core, shielded. D1: >2A continuous, fast Trr, reverse breakdown >250V. Q1: gate charge <50nC, rDS(ON) <100mOhm.
DIGIT CONTROL
DIGIT 1 FEEDBACK CONTROL

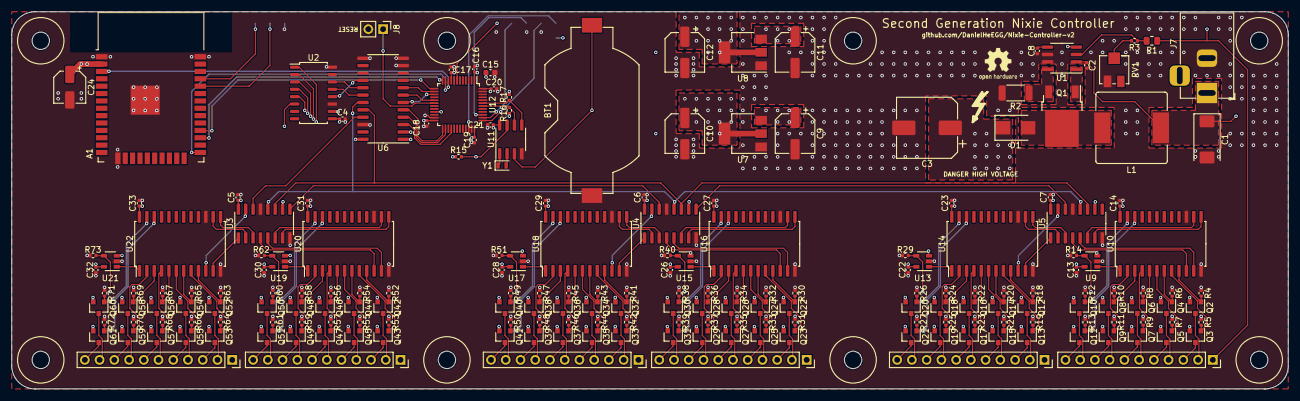
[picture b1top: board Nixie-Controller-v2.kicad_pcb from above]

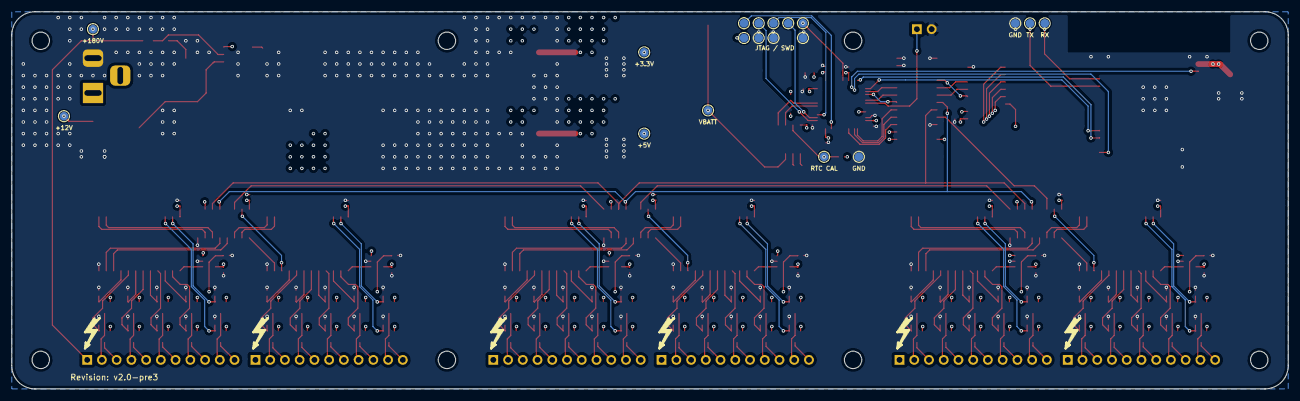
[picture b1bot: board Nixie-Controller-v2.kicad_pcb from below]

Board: 4 copper layers, 220.0 x 65.0 mm, 220 parts (19 on the bottom side), 206 nets.

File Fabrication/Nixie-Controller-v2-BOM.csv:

Reference, Quantity, Value, Footprint, Datasheet, Manufacturer, Part#
A1 ,1,"ESP32-WROOM-32E","RF_Module:ESP32-WROOM-32",""
BT1 ,1,"BACKUP","Battery:BatteryHolder_Keystone_1058_1x2032","~","Keystone","1058"
C1 ,1,"100uF","Capacitor_Tantalum_SMD:CP_EIA-7343-43_Kemet-X","~","Kemet","T510X107M020ATE045"
C15 ,1,"4.7uF","Capacitor_SMD:C_0603_1608Metric","~","Yageo","CC0603MRX5R5BB475"
C24 ,1,"47uF","Capacitor_SMD:CP_Elec_5x5.3","~","Nichicon","UWF0J470MCL1GB"
C3 ,1,"10uF","Capacitor_SMD:CP_Elec_10x10","~","Nichicon","UUX2E100MNL1GS"
C2 C4 C5 C6 C7 C8 C13 C14 C16 C17 C18 C19 C20 C21 C22 C23 C26 C27 C28 C29 C30 C31 C32 C33 ,24,"100nF","Capacitor_SMD:C_0402_1005Metric","~","Yageo","CC0402KRX7R8BB104"
C9 C10 C11 C12 ,4,"10uF","Capacitor_SMD:CP_Elec_6.3x7.7","~","Nichicon","UUL1H100MCL1GS"
D1 ,1,"~","Diode_SMD:D_SMB","~","Vishay","ES2F"
L1 ,1,"47uH","Inductor_SMD:L_Bourns_SRR1210A","~","Bourns","SRR1210A-470M"
Q1 ,1,"~","Package_TO_SOT_SMD:TO-252-2","~","IXYS","IXFY26N30X3"
Q2 Q3 Q4 Q5 Q6 Q7 Q8 Q9 Q10 Q11 Q12 Q13 Q14 Q15 Q16 Q17 Q18 Q19 Q20 Q21 Q22 Q23 Q24 Q25 Q26 Q27 Q28 Q29 Q30 Q31 Q32 Q33 Q34 Q35 Q36 Q37 Q38 Q39 Q40 Q41 Q42 Q43 Q44 Q45 Q46 Q47 Q48 Q49 Q50 Q51 Q52 Q53 Q54 Q55 Q56 Q57 Q58 Q59 Q60 Q61 ,60,"~","Package_TO_SOT_SMD:SOT-23","~","Nexperia","MMBTA42"
R1 ,1,"1.2M","Resistor_SMD:R_0805_2012Metric","~","Yageo","RC0805FR-071M2L"
R14 R29 R40 R51 R62 R73 ,6,"470","Resistor_SMD:R_0402_1005Metric","~","Yageo","RC0402FR-07470RL"
R2 ,1,"0.05","Resistor_SMD:R_2010_5025Metric","~","Yageo","PE2010FKE070R05L"
R3 R4 R5 R6 R7 R8 R9 R10 R11 R12 R13 R15 R16 R17 R18 R19 R20 R21 R22 R23 R24 R25 R26 R27 R30 R31 R32 R33 R34 R35 R36 R37 R38 R39 R41 R42 R43 R44 R45 R46 R47 R48 R49 R50 R52 R53 R54 R55 R56 R57 R58 R59 R60 R61 R63 R64 R65 R66 R67 R68 R69 R70 R71 R72 ,64,"6.8K","Resistor_SMD:R_0402_1005Metric","~","Yageo","RC0402FR-076K8L"
RV1 ,1,"5K","Potentiometer_SMD:Potentiometer_Bourns_3214J_Horizontal","~","Bourns","3214J-1-502E"
U1 ,1,"MAX1771","Package_SO:SOIC-8_3.9x4.9mm_P1.27mm","~","Maxim","MAX1771CSA"
U11 ,1,"M41T01","Package_SO:SOIC-8_3.9x4.9mm_P1.27mm","~","ST Micro","M41T01M6F"
U12 ,1,"STM32F103C8","Package_QFP:LQFP-48_7x7mm_P0.5mm","~","ST Micro","STM32F103C8T6"
U9 U13 U15 U17 U19 U21 ,6,"OPA180","Package_TO_SOT_SMD:SOT-23-5","~","TI","OPA180IDBVT"
U10 U14 U16 U18 U20 U22 ,6,"74HC4067","Package_SO:SOIC-24W_7.5x15.4mm_P1.27mm","~","TI","CD74HC4067M"
U2 ,1,"BH2226","Package_SO:SOIC-16_4.55x10.3mm_P1.27mm","~","Rohm Semi","BH2226F-E2"
U3 U4 U5 ,3,"74HC595","Package_SO:SOIC-16_3.9x9.9mm_P1.27mm","~","TI","CD74HC595M"
U6 ,1,"SN74LVCC3245A","Package_SO:SO-24_5.3x15mm_P1.27mm","~","TI","SN74LVCC3245ANSR"
U7 ,1,"NCP1117-5.0","Package_TO_SOT_SMD:SOT-223-3_TabPin2","~","ON Semi","NCP1117LPST50T3G"
U8 ,1,"NCP1117-3.3","Package_TO_SOT_SMD:SOT-223-3_TabPin2","~","ON Semi","NCP1117LPST33T3G"
Y1 ,1,"32.768KHz","Crystal:Crystal_SMD_2012-2Pin_2.0x1.2mm","~","Seiko","SC20S-12.5PF20PPM"
